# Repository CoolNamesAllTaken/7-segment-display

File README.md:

# 7-segment-display
Cascade-able 7 segment display board.

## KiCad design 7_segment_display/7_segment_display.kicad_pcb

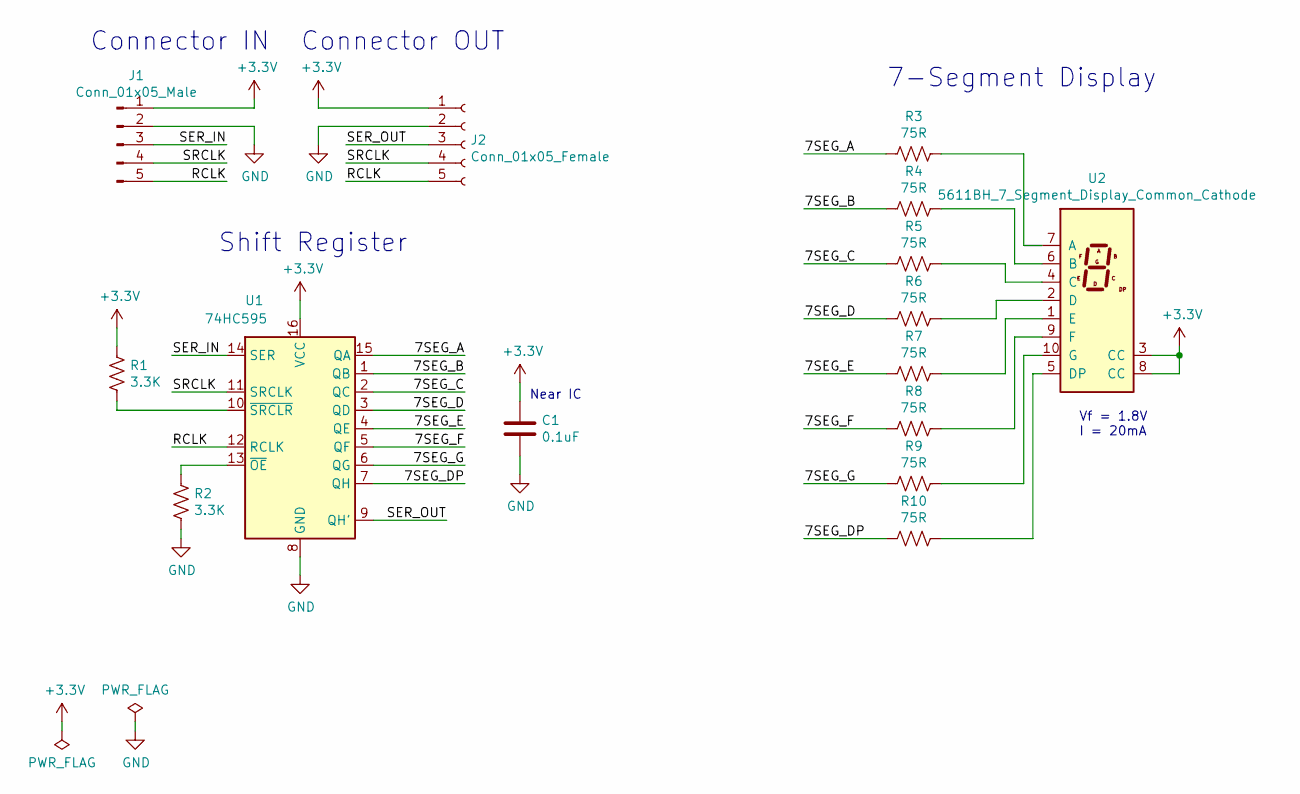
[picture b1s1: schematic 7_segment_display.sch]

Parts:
C1: 0.1uF; C_0603_1608Metric
J1: Conn_01x05_Male; PinHeader_1x05_P2.54mm_Horizontal
J2: Conn_01x05_Female; PinSocket_1x05_P2.54mm_Horizontal
R1, R2: 3.3K; R_0603_1608Metric
R3, R4, R5, R6, R7, R8, R9, R10: 75R; R_0603_1608Metric
U1: 74HC595; SOP-16_4.4x10.4mm_P1.27mm
U2: 5611BH_7_Segment_Display_Common_Cathode; 5611BH

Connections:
+3V3: C1.1, J1.1, J2.1, R1.1, U1.16 (VCC), U2.3 (CC), U2.8 (CC)
/7SEG_A: R3.2, U1.15 (QA)
/7SEG_B: R4.2, U1.1 (QB)
/7SEG_C: R5.2, U1.2 (QC)
/7SEG_D: R6.2, U1.3 (QD)
/7SEG_DP: R10.2, U1.7 (QH)
/7SEG_E: R7.2, U1.4 (QE)
/7SEG_F: R8.2, U1.5 (QF)
/7SEG_G: R9.2, U1.6 (QG)
/RCLK: J1.5, J2.5, U1.12 (RCLK)
/SER_IN: J1.3, U1.14 (SER)
/SER_OUT: J2.3, U1.9 (QH')
/SRCLK: J1.4, J2.4, U1.11 (SRCLK)
GND: C1.2, J1.2, J2.2, R2.2, U1.8 (GND)
unnamed: R1.2, U1.10 (~SRCLR)
unnamed: R2.1, U1.13 (~OE)
unnamed: R3.1, U2.7 (A)
unnamed: R4.1, U2.6 (B)
unnamed: R5.1, U2.4 (C)
unnamed: R6.1, U2.2 (D)
unnamed: R7.1, U2.1 (E)
unnamed: R8.1, U2.9 (F)
unnamed: R9.1, U2.10 (G)
unnamed: R10.1, U2.5 (DP)

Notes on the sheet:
Vf = 1.8V I = 20mA
Connector IN
Connector OUT
Near IC
Shift Register
7-Segment Display

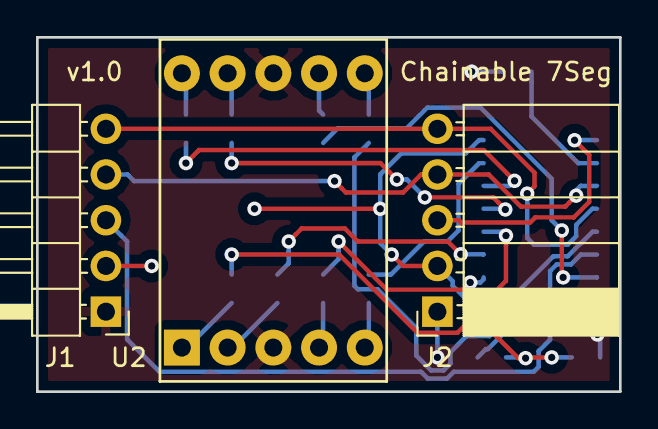
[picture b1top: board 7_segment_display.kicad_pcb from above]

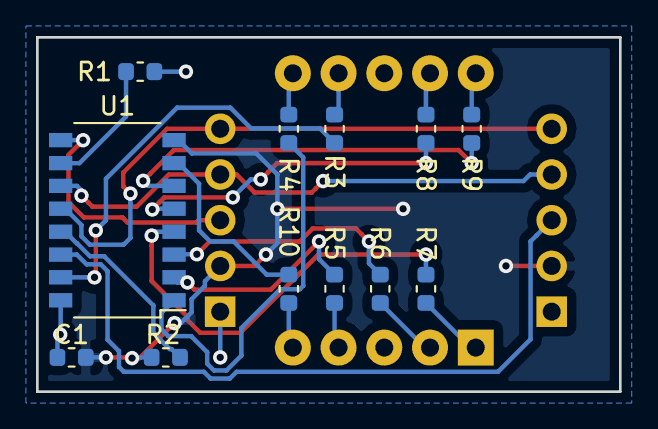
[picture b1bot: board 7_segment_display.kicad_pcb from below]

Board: 2 copper layers, 32.4 x 19.7 mm, 15 parts (12 on the bottom side), 24 nets.

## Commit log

2019-05-13 Make first version
2019-05-13 Make one that actually works
    Use correct pin footprint for 7 segment display
2019-05-18 Cleanup
2020-08-02 Dump leftovers
